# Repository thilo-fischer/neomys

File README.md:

# neomys
Driver software for my Teensy-based DIY keyboard for the Neo2 keyboard layout

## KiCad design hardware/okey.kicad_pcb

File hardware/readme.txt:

Directory includes the schematics and PCB design used to build hardware of Okey adaptations.

The EDA software used is KiCad, http://kicad-pcb.org/. As Okey, KiCad is open source such that anybody can use the software free of charge. (There are some free versions of commercial EDA software available, but those have special restrictions which makes them inapplicable for most Okey PCBs, e.g. PCB sizes below 80 x 100 mm.)

Most schematics and PCB files use parts not (yet) available from the standard libraries that come with KiCad. These parts are taken from 3rd party library files that can be found in the internet. Due to unclear license and copyright constraints of those 3rd party library, these library files are not included in the Okey repository. Currently, these parts listed below are taken from the referenced libraries:

Cherry MX switches
  http://www.key64.org/downloads/key64-20120707.tgz => cherry.lib

7-stage binary counter 4024
  http://www.kicadlib.org/modules/gajda_cmosieee.lib.zip

8 bit SIPO shift latch register 4094N
  https://github.com/musa/kicad-library/blob/master/library/40xx.lib

Todo-List

- Constoller board: Change BCE Transistors to more common CBE Transistors
- Extra buttons board: Adapt button footprint to match 2.54 mm raster *and* 4.50/6.50 mm (6 mm) buttons (e.g. JTP-1130)

Notes

#Grid used to place Cherry MX switches and route tracks: 18.5mm x 18.5mm, 1.85mm x 1.85mm

Grid used to place Cherry MX switches: 18.415mm x 18.415mm, 2.301875mm x 0.3175mm
  2.54 * 7.25 = 18.415
  18.415 / 8 = 2.301875
  2.54 / 8 = 0.3175

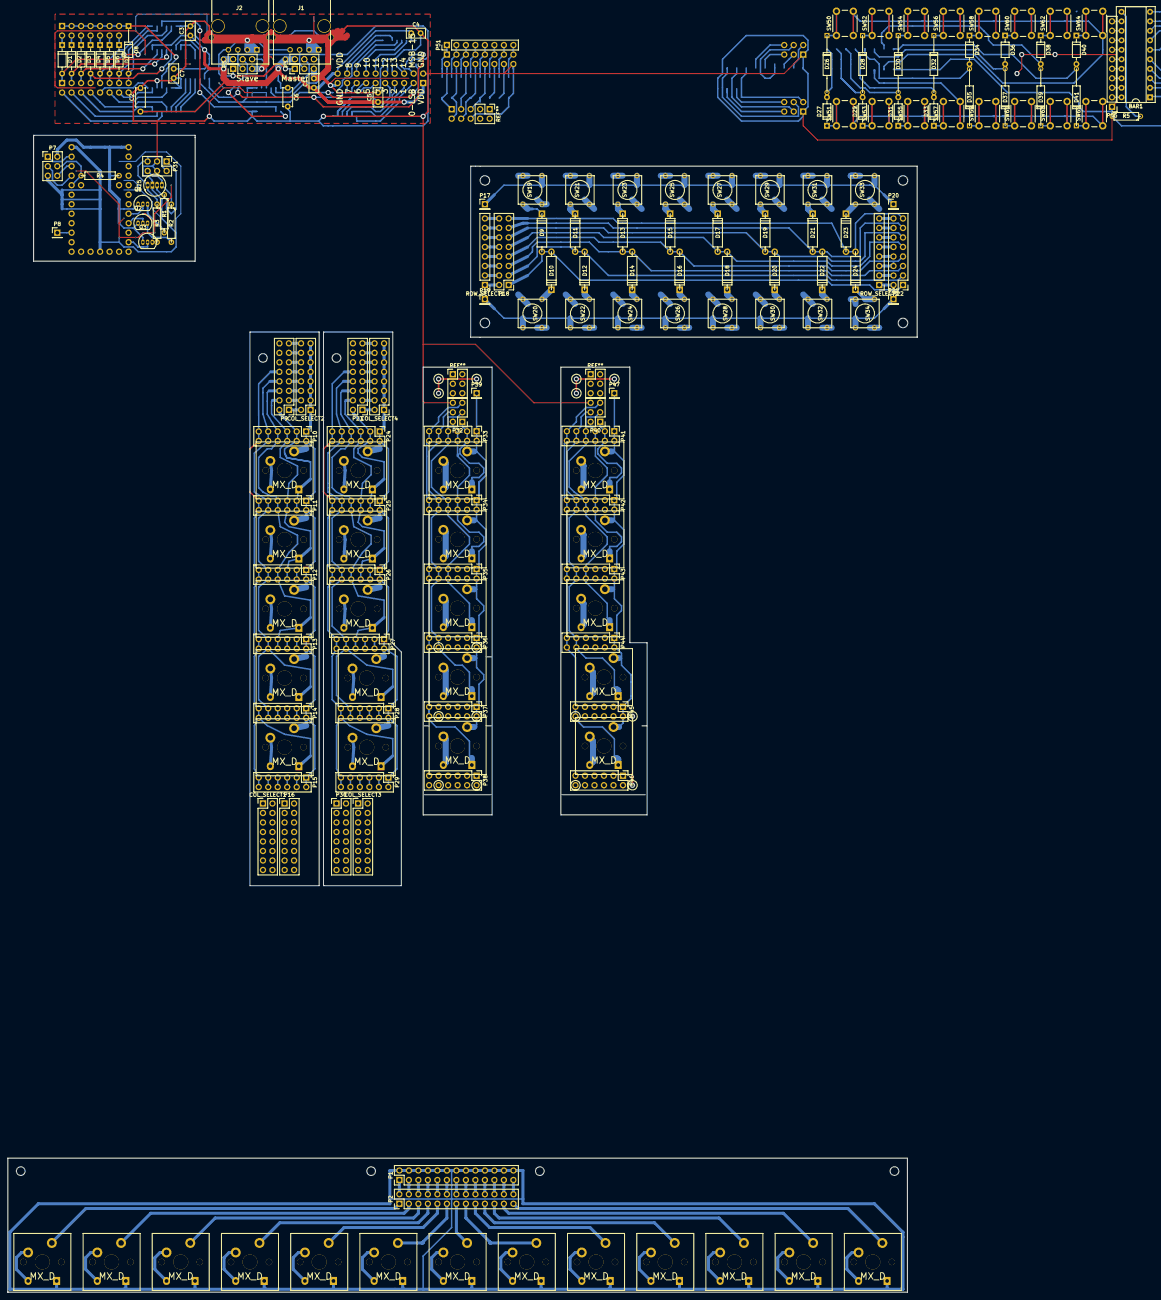
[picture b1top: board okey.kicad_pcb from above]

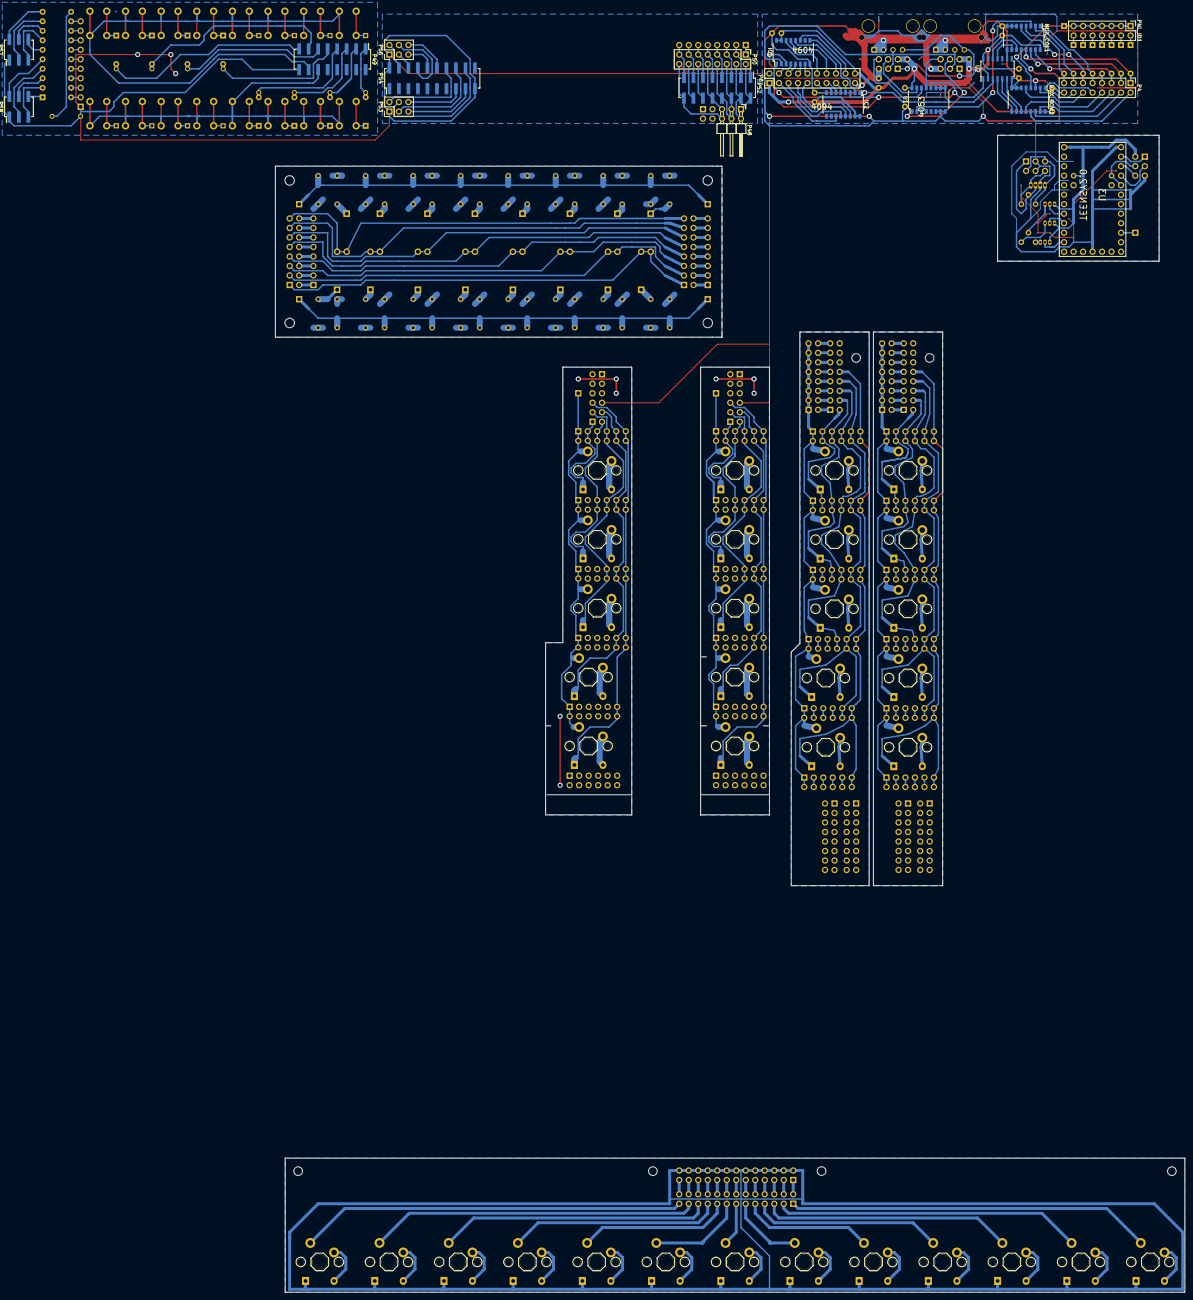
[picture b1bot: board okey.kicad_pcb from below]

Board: 2 copper layers, 196 parts (18 on the bottom side), 300 nets.

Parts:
BAR1: DOT-BAR2; DIP-20_W7.62mm_Socket
C1: 1uF; C_Disc_D5.0mm_W2.5mm_P2.50mm
C2, C6: 100nF; C_Disc_D5.0mm_W2.5mm_P5.00mm
C3, C4, C5, C7: 100nF; C_Disc_D5.0mm_W2.5mm_P2.50mm
COL_SELECT1, COL_SELECT2, COL_SELECT3, COL_SELECT4: CONN_02X08; Pin_Header_Straight_2x08_Pitch2.54mm
D1, D2, D3, D4, D5, D6, D7, D27, D29, D31, D33, D34, D36, D38, D40: D; D_DO-35_SOD27_P7.62mm_Horizontal
D8: D; D_DO-35_SOD27_P12.70mm_Horizontal
D9, D10, D11, D12, D13, D14, D15, D16, D17, D18, D19, D20, D21, D22, D23, D24: D; D4
D25: LED_RCBG; LED-RGB-5MM_Common_Cathode
D26, D28, D30, D32, D35, D37, D39, D41: D; D6_small
IC1, IC2: 4094N; SOP-16_4.4x10.4mm_Pitch1.27mm
J1, J2: RJ45; RJ45_8G
MUX_COL1: 4051; SOP-16_4.4x10.4mm_Pitch1.27mm
MUX_ROW1: 4051; SOP-16_4.4x10.4mm_Pitch1.27mm
P1: ROW_JMP; Pin_Header_Straight_2x13_Pitch2.54mm
P2: CONN_02X13; Pin_Header_Straight_2x13_Pitch2.54mm
P3, P5, P7, P31, P32, P40: CONN_02X03; Pin_Header_Straight_2x03_Pitch2.54mm
P4, P9, P16, P18, P22, P23, P30, P50: CONN_02X08; Pin_Header_Straight_2x08_Pitch2.54mm
P6: CONN_02X10; Pin_Header_Straight_2x10_Pitch2.54mm
P8, P17, P19, P20, P21, P39, P47: CONN_01X01; Pin_Header_Straight_1x01_Pitch2.54mm
P10, P11, P12, P13, P14, P15, P24, P25, P26, P27, P28, P29, P33, P34, P35, P36, P37, P38, P41, P42, P43, P44, P45, P46: CONN_02X06; Pin_Header_Straight_2x06_Pitch2.54mm
P48: CONN_02X03; Pin_Header_Angled_2x03_Pitch2.54mm
P49, P52: CONN_02X08; Pin_Header_Straight_2x08_Pitch2.54mm_SMD
P51: CONN_01X08; Pin_Header_Straight_1x08_Pitch2.54mm
P53, P56: CONN_01X06; Pin_Header_Straight_2x03_Pitch2.54mm
P54: CONN_02X10; Pin_Header_Straight_2x10_Pitch2.54mm_SMD
P55: R_SIP_x9_390; Pin_Header_Straight_1x10_Pitch2.54mm
P57, P58: CONN_01X06; Pin_Header_Straight_2x03_Pitch2.54mm_SMD
PNL_ID1: CONN_02X07; Pin_Header_Straight_2x07_Pitch2.54mm
Q1, Q2, Q3: Q_NPN_CBE; TO-92_Inline_Narrow_Oval
R1, R2, R3, R4: R; R4
R5: R270; R3
ROW_SELECT1, ROW_SELECT2: CONN_01X08; Pin_Header_Straight_1x08_Pitch2.54mm
SW1, SW2, SW3, SW4, SW5, SW6, SW7, SW8, SW9, SW10, SW11, SW12, SW13, SW14, SW15, SW16, SW17, SW18, SW35, SW36, SW37, SW38, SW39, SW40, SW41, SW42, SW43, SW44, SW45, SW46, SW47, SW48, SW49: MX_D; SW_PCB_4PIN
SW19, SW20, SW21, SW22, SW23, SW24, SW25, SW26, SW27, SW28, SW29, SW30, SW31, SW32, SW33, SW34: SW_PUSH; SW_PUSH_SMALL
SW50, SW51, SW52, SW53, SW54, SW55, SW56, SW57, SW58, SW59, SW60, SW61, SW62, SW63, SW64, SW65: SW_PUSH; SW_PUSH_6mm
U1: 4053; SOP-16_4.4x10.4mm_Pitch1.27mm
U2: 4024; SOIC-14_3.9x8.7mm_Pitch1.27mm
U3: TEENSY2.0; TEENSY_2.0

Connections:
/Cherry-MX Switches Row 3x up to 8x /ROW: P1.2, P1.4, P1.6, P1.8, P1.10, P1.12, P1.14, P1.16, P1.18, P1.20, P1.22, P1.24, P1.26, SW1.4, SW2.4, SW3.4, SW4.4, SW5.4, SW6.4, SW7.4, SW8.4, SW9.4, SW10.4, SW11.4, SW12.4, SW13.4
/Panel Generic SPI01/PNL_BUS_OUT: J2.4, P5.4, U1.1
/Panel Generic SPI01/clock: J1.2, P3.6, U1.14
/Panel Generic SPI01/miso: J1.4, P3.4, U1.15
/Panel Generic SPI01/reset: J1.7, J2.7, P3.1, P5.1, U2.2
GND: C1.2, C2.2, C3.2, C4.2, C5.2, C6.2, C7.2, D25.2, IC1.8, IC2.8, J1.1, J1.3, J1.9, J2.1, J2.3, J2.9, MUX_COL1.6, MUX_COL1.7, MUX_COL1.8, MUX_ROW1.3, MUX_ROW1.6, MUX_ROW1.7, MUX_ROW1.8, P3.5, P4.16, P5.5, P6.2, P6.19, P7.5, P31.3, P31.4, P32.6, P40.6, P48.6, P49.16, P50.16, P52.16, P53.1, P54.2, P54.19, P55.1, P56.1, P57.1, P58.1, R5.2, U1.6, U1.7, U1.8, U2.7, U3.15, U3.29
unnamed: BAR1.1, P58.6
unnamed: BAR1.2, P58.5
unnamed: BAR1.3, P58.4
unnamed: BAR1.4, P58.3
unnamed: BAR1.5, P58.2
unnamed: BAR1.6, P57.6
unnamed: BAR1.7, P57.5
unnamed: BAR1.8, P57.4
unnamed: BAR1.9, P57.3
unnamed: BAR1.10, P57.2
unnamed: BAR1.11, R5.1
unnamed: BAR1.12, P55.10
unnamed: BAR1.13, P55.9
unnamed: BAR1.14, P55.8
unnamed: BAR1.15, P55.7
unnamed: BAR1.16, P55.6
unnamed: BAR1.17, P55.5
unnamed: BAR1.18, P55.4
unnamed: BAR1.19, P55.3
unnamed: BAR1.20, P55.2
unnamed: COL_SELECT1.1, COL_SELECT1.3, COL_SELECT1.5, COL_SELECT1.7, COL_SELECT1.9, COL_SELECT1.11, COL_SELECT1.13, COL_SELECT1.15, COL_SELECT2.1, COL_SELECT2.3, COL_SELECT2.5, COL_SELECT2.7, COL_SELECT2.9, COL_SELECT2.11, COL_SELECT2.13, COL_SELECT2.15, P10.1, P10.2, P11.1, P11.2, P12.1, P12.2, P13.1, P13.2, P14.1, P14.2, P15.1, P15.2, SW14.1, SW15.1, SW16.1, SW17.1, SW18.1
unnamed: COL_SELECT1.2, P16.1
unnamed: COL_SELECT1.4, P16.3
unnamed: COL_SELECT1.6, P16.5
unnamed: COL_SELECT1.8, P16.7
unnamed: COL_SELECT1.10, P16.9
unnamed: COL_SELECT1.12, P16.11
unnamed: COL_SELECT1.14, P16.13
unnamed: COL_SELECT1.16, P16.15
unnamed: COL_SELECT2.2, P9.1
unnamed: COL_SELECT2.4, P9.3
unnamed: COL_SELECT2.6, P9.5
unnamed: COL_SELECT2.8, P9.7
unnamed: COL_SELECT2.10, P9.9
unnamed: COL_SELECT2.12, P9.11
unnamed: COL_SELECT2.14, P9.13
unnamed: COL_SELECT2.16, P9.15
unnamed: COL_SELECT3.1, COL_SELECT3.3, COL_SELECT3.5, COL_SELECT3.7, COL_SELECT3.9, COL_SELECT3.11, COL_SELECT3.13, COL_SELECT3.15, COL_SELECT4.1, COL_SELECT4.3, COL_SELECT4.5, COL_SELECT4.7, COL_SELECT4.9, COL_SELECT4.11, COL_SELECT4.13, COL_SELECT4.15, P24.1, P24.2, P25.1, P25.2, P26.1, P26.2, P27.1, P27.2, P28.1, P28.2, P29.1, P29.2, SW35.1, SW36.1, SW37.1, SW38.1, SW39.1
unnamed: COL_SELECT3.2, P30.1
unnamed: COL_SELECT3.4, P30.3
unnamed: COL_SELECT3.6, P30.5
unnamed: COL_SELECT3.8, P30.7
unnamed: COL_SELECT3.10, P30.9
unnamed: COL_SELECT3.12, P30.11
unnamed: COL_SELECT3.14, P30.13
unnamed: COL_SELECT3.16, P30.15
unnamed: COL_SELECT4.2, P23.1
unnamed: COL_SELECT4.4, P23.3
unnamed: COL_SELECT4.6, P23.5
unnamed: COL_SELECT4.8, P23.7
unnamed: COL_SELECT4.10, P23.9
unnamed: COL_SELECT4.12, P23.11
unnamed: COL_SELECT4.14, P23.13
unnamed: COL_SELECT4.16, P23.15
unnamed: D1.1, PNL_ID1.2
unnamed: D1.2, MUX_COL1.13, P4.1
unnamed: D2.1, PNL_ID1.4
unnamed: D2.2, MUX_COL1.14, P4.3
unnamed: D3.1, PNL_ID1.6
unnamed: D3.2, MUX_COL1.15, P4.5
unnamed: D4.1, PNL_ID1.8
unnamed: D4.2, MUX_COL1.12, P4.7
unnamed: D5.1, PNL_ID1.10
unnamed: D5.2, MUX_COL1.1, P4.9
unnamed: D6.1, PNL_ID1.12
unnamed: D6.2, MUX_COL1.5, P4.11
unnamed: D7.1, PNL_ID1.14
unnamed: D7.2, MUX_COL1.2, P4.13
unnamed: D8.1, MUX_ROW1.4, PNL_ID1.1, PNL_ID1.3, PNL_ID1.5, PNL_ID1.7, PNL_ID1.9, PNL_ID1.11, PNL_ID1.13
unnamed: D8.2, MUX_COL1.4, P4.15
unnamed: D9.1, SW19.1
unnamed: D10.1, SW20.1
unnamed: D9.2, D10.2, P18.1, P22.1
unnamed: D11.1, SW21.1
unnamed: D11.2, D12.2, P18.3, P22.3
unnamed: D12.1, SW22.1
unnamed: D13.1, SW23.1
unnamed: D13.2, D14.2, P18.5, P22.5
unnamed: D14.1, SW24.1
unnamed: D15.1, SW25.1
unnamed: D15.2, D16.2, P18.7, P22.7
unnamed: D16.1, SW26.1
unnamed: D17.1, SW27.1
unnamed: D17.2, D18.2, P18.9, P22.9
unnamed: D18.1, SW28.1
unnamed: D19.1, SW29.1
unnamed: D19.2, D20.2, P18.11, P22.11
unnamed: D20.1, SW30.1
unnamed: D21.1, SW31.1
unnamed: D21.2, D22.2, P18.13, P22.13
unnamed: D22.1, SW32.1
unnamed: D23.1, SW33.1
unnamed: D23.2, D24.2, P18.15, P22.15
unnamed: D24.1, SW34.1
unnamed: D25.1, P31.2, P31.5, R3.1
unnamed: D25.3, P31.1, R1.1
unnamed: D25.4, P31.6, R2.1
unnamed: D26.1, SW50.1
unnamed: D26.2, D27.2, P49.1
unnamed: D27.1, SW51.1
unnamed: D28.1, SW52.1
unnamed: D28.2, D29.2, P49.3
unnamed: D29.1, SW53.1
unnamed: D30.1, SW54.1
unnamed: D30.2, D31.2, P49.5
unnamed: D31.1, SW55.1
unnamed: D32.1, SW56.1
unnamed: D32.2, D33.2, P49.7
unnamed: D33.1, SW57.1
unnamed: D34.1, SW58.1
unnamed: D34.2, D35.2, P49.9
unnamed: D35.1, SW59.1
unnamed: D36.1, SW60.1
unnamed: D36.2, D37.2, P49.11
unnamed: D37.1, SW61.1
unnamed: D38.1, SW62.1
unnamed: D38.2, D39.2, P49.13
unnamed: D39.1, SW63.1
unnamed: D40.1, SW64.1
unnamed: D40.2, D41.2, P49.15
unnamed: D41.1, SW65.1
unnamed: IC1.1, IC2.1, U1.9, U1.10, U1.11, U2.3
unnamed: IC1.2, J1.5, J2.5, P3.3, P5.3
unnamed: IC1.3, IC2.3, U1.12, U2.1
unnamed: IC1.4, P6.4
unnamed: IC1.5, P6.6
unnamed: IC1.6, P6.8
unnamed: IC1.7, P6.10
unnamed: IC1.9, IC2.2
unnamed: IC1.11, P6.18
unnamed: IC1.12, P6.16
unnamed: IC1.13, P6.14
unnamed: IC1.14, P6.12
unnamed: IC2.4, P6.17
unnamed: IC2.5, P6.15
unnamed: IC2.6, P6.13
unnamed: IC2.7, P6.11
unnamed: IC2.11, P6.3
unnamed: IC2.12, P6.5
unnamed: IC2.13, P6.7
unnamed: IC2.14, P6.9
unnamed: J2.2, P5.6, U1.13
unnamed: MUX_COL1.3, U1.2
unnamed: MUX_COL1.9, U2.9
unnamed: MUX_COL1.10, U2.11
unnamed: MUX_COL1.11, U2.12
unnamed: MUX_ROW1.1, P4.10
unnamed: MUX_ROW1.2, P4.14
unnamed: MUX_ROW1.5, P4.12
unnamed: MUX_ROW1.9, U2.4
unnamed: MUX_ROW1.10, U2.5
unnamed: MUX_ROW1.11, U2.6
unnamed: MUX_ROW1.12, P4.8
unnamed: MUX_ROW1.13, P4.2
unnamed: MUX_ROW1.14, P4.4
unnamed: MUX_ROW1.15, P4.6
unnamed: P1.1, P2.2
unnamed: P1.3, P2.4
unnamed: P1.5, P2.6
unnamed: P1.7, P2.8
unnamed: P1.9, P2.10
unnamed: P1.11, P2.12
unnamed: P1.13, P2.14
unnamed: P1.15, P2.16
unnamed: P1.17, P2.18
unnamed: P1.19, P2.20
unnamed: P1.21, P2.22
unnamed: P1.23, P2.24
unnamed: P1.25, P2.26
unnamed: P2.1, SW4.1
unnamed: P2.3, SW5.1
unnamed: P2.5, SW6.1
unnamed: P2.7, SW7.1
unnamed: P2.9, SW8.1
unnamed: P2.11, SW1.1
unnamed: P2.13, SW2.1
unnamed: P2.15, SW3.1
unnamed: P2.17, SW9.1
unnamed: P2.19, SW10.1
unnamed: P2.21, SW11.1
unnamed: P2.23, SW12.1
unnamed: P2.25, SW13.1
unnamed: P7.1, U3.28
unnamed: P7.3, U3.26
unnamed: P7.4, R4.2, U3.25
unnamed: P7.6, U3.27
unnamed: P8.1, U3.20
unnamed: P9.2, P10.3, P10.4, P11.3, P11.4, P12.3, P12.4, P13.3, P13.4, P14.3, P14.4, P15.3, P15.4, P16.2, SW14.4
unnamed: P9.4, P10.5, P10.6, P11.5, P11.6, P12.5, P12.6, P13.5, P13.6, P14.5, P14.6, P15.5, P15.6, P16.4, SW15.4
unnamed: P9.6, P10.7, P10.8, P11.7, P11.8, P12.7, P12.8, P13.7, P13.8, P14.7, P14.8, P15.7, P15.8, P16.6, SW16.4
unnamed: P9.8, P10.9, P10.10, P11.9, P11.10, P12.9, P12.10, P13.9, P13.10, P14.9, P14.10, P15.9, P15.10, P16.8, SW17.4
unnamed: P9.10, P10.11, P10.12, P11.11, P11.12, P12.11, P12.12, P13.11, P13.12, P14.11, P14.12, P15.11, P15.12, P16.10, SW18.4
unnamed: P17.1, P20.1, SW19.2, SW21.2, SW23.2, SW25.2, SW27.2, SW29.2, SW31.2, SW33.2
unnamed: P18.2, ROW_SELECT1.1
unnamed: P18.4, ROW_SELECT1.2
unnamed: P18.6, ROW_SELECT1.3
unnamed: P18.8, ROW_SELECT1.4
unnamed: P18.10, ROW_SELECT1.5
unnamed: P18.12, ROW_SELECT1.6
unnamed: P18.14, ROW_SELECT1.7
unnamed: P18.16, ROW_SELECT1.8
unnamed: P19.1, P21.1, SW20.2, SW22.2, SW24.2, SW26.2, SW28.2, SW30.2, SW32.2, SW34.2
unnamed: P22.2, ROW_SELECT2.1
unnamed: P22.4, ROW_SELECT2.2
unnamed: P22.6, ROW_SELECT2.3
unnamed: P22.8, ROW_SELECT2.4
unnamed: P22.10, ROW_SELECT2.5
unnamed: P22.12, ROW_SELECT2.6
unnamed: P22.14, ROW_SELECT2.7
unnamed: P22.16, ROW_SELECT2.8
unnamed: P23.2, P24.3, P24.4, P25.3, P25.4, P26.3, P26.4, P27.3, P27.4, P28.3, P28.4, P29.3, P29.4, P30.2, SW35.4
unnamed: P23.4, P24.5, P24.6, P25.5, P25.6, P26.5, P26.6, P27.5, P27.6, P28.5, P28.6, P29.5, P29.6, P30.4, SW36.4
unnamed: P23.6, P24.7, P24.8, P25.7, P25.8, P26.7, P26.8, P27.7, P27.8, P28.7, P28.8, P29.7, P29.8, P30.6, SW37.4
unnamed: P23.8, P24.9, P24.10, P25.9, P25.10, P26.9, P26.10, P27.9, P27.10, P28.9, P28.10, P29.9, P29.10, P30.8, SW38.4
unnamed: P23.10, P24.11, P24.12, P25.11, P25.12, P26.11, P26.12, P27.11, P27.12, P28.11, P28.12, P29.11, P29.12, P30.10, SW39.4
unnamed: P32.1, P33.3, P33.4, SW40.4
unnamed: P32.2, P33.5, P33.6, P34.5, P34.6, SW41.4
unnamed: P32.3, P33.7, P33.8, P34.7, P34.8, P35.7, P35.8, SW42.4
unnamed: P32.4, P33.9, P33.10, P34.9, P34.10, P35.9, P35.10, P36.9, P36.10, SW43.4
unnamed: P32.5, P33.11, P33.12, P34.11, P34.12, P35.11, P35.12, P36.11, P36.12, P37.11, P37.12, SW44.4
unnamed: P33.1, P33.2, P34.1, P34.2, P35.1, P35.2, P36.1, P36.2, P37.1, P37.2, P39.1, SW40.1, SW41.1, SW42.1, SW43.1, SW44.1
unnamed: P40.1, P41.3, P41.4, SW45.4
unnamed: P40.2, P41.5, P41.6, P42.5, P42.6, SW46.4
unnamed: P40.3, P41.7, P41.8, P42.7, P42.8, P43.7, P43.8, SW47.4
unnamed: P40.4, P41.9, P41.10, P42.9, P42.10, P43.9, P43.10, P44.9, P44.10, SW48.4
unnamed: P40.5, P41.11, P41.12, P42.11, P42.12, P43.11, P43.12, P44.11, P44.12, P45.11, P45.12, SW49.4
unnamed: P41.1, P41.2, P42.1, P42.2, P43.1, P43.2, P44.1, P44.2, P45.1, P45.2, P47.1, SW45.1, SW46.1, SW47.1, SW48.1, SW49.1
unnamed: P48.1, P50.2, P52.2
unnamed: P48.2, P50.4, P52.4
unnamed: P48.3, P50.6, P52.6
unnamed: P48.4, P50.8, P52.8
unnamed: P48.5, P50.10, P52.10
unnamed: P49.12, SW51.2, SW53.2, SW55.2, SW57.2, SW59.2, SW61.2, SW63.2, SW65.2
unnamed: P49.14, SW50.2, SW52.2, SW54.2, SW56.2, SW58.2, SW60.2, SW62.2, SW64.2
unnamed: P50.1, P51.1, P52.1
unnamed: P50.3, P51.2, P52.3
unnamed: P50.5, P51.3, P52.5
unnamed: P50.7, P51.4, P52.7
unnamed: P50.9, P51.5, P52.9
unnamed: P50.11, P51.6, P52.11
unnamed: P50.12, P52.12
unnamed: P50.13, P51.7, P52.13
unnamed: P50.14, P52.14
unnamed: P50.15, P51.8, P52.15
unnamed: P53.2, P54.14
unnamed: P53.3, P54.16
unnamed: P53.4, P54.18
unnamed: P53.5, P54.17
unnamed: P53.6, P54.15
unnamed: P54.4, P56.2
unnamed: P54.6, P56.3
unnamed: P54.8, P56.4
unnamed: P54.10, P56.5
unnamed: P54.12, P56.6
unnamed: Q1.2, U3.8
unnamed: Q1.3, R1.2
unnamed: Q2.2, U3.9
unnamed: Q2.3, R2.2
unnamed: Q3.2, U3.11
unnamed: Q3.3, R3.2
unnamed: SW1.2, SW1.3
unnamed: SW2.2, SW2.3
unnamed: SW3.2, SW3.3
unnamed: SW4.2, SW4.3
unnamed: SW5.2, SW5.3
unnamed: SW6.2, SW6.3
unnamed: SW7.2, SW7.3
unnamed: SW8.2, SW8.3
unnamed: SW9.2, SW9.3
unnamed: SW10.2, SW10.3
unnamed: SW11.2, SW11.3
unnamed: SW12.2, SW12.3
unnamed: SW13.2, SW13.3
unnamed: SW14.2, SW14.3
unnamed: SW15.2, SW15.3
unnamed: SW16.2, SW16.3
unnamed: SW17.2, SW17.3
unnamed: SW18.2, SW18.3
unnamed: SW35.2, SW35.3
unnamed: SW36.2, SW36.3
unnamed: SW37.2, SW37.3
unnamed: SW38.2, SW38.3
unnamed: SW39.2, SW39.3
unnamed: SW40.2, SW40.3
unnamed: SW41.2, SW41.3
unnamed: SW42.2, SW42.3
unnamed: SW43.2, SW43.3
unnamed: SW44.2, SW44.3
unnamed: SW45.2, SW45.3
unnamed: SW46.2, SW46.3
unnamed: SW47.2, SW47.3
unnamed: SW48.2, SW48.3
unnamed: SW49.2, SW49.3
VDD: C1.1, C2.1, C3.1, C4.1, C5.1, C6.1, C7.1, IC1.15, IC1.16, IC2.15, IC2.16, J1.6, J1.8, J2.6, J2.8, MUX_COL1.16, MUX_ROW1.16, P3.2, P5.2, P6.1, P6.20, P7.2, P54.1, P54.20, Q1.1, Q2.1, Q3.1, R4.1, U1.16, U2.14, U3.1

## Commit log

2015-02-04 fixed some compile issues
2015-02-04 fix compile errors
2015-02-04 drop F-key row
2015-02-04 key mapping for DE
2015-02-06 split to several files
2015-02-06 started to implement key press evluation
2015-02-06 refactor keymappings.h
2015-02-07 started implementation of approch to communicate key_ids of all pressed keys from slave to master
2015-02-07 started implementation of approch to communicate key_ids of only changed keys from slave to master
2015-02-08 restructure keymap array definition
2015-02-10 fix keymap table (DE ROW_NUM level2)
2015-02-10 restructure and refactor keymappings
2015-02-11 finished writing down all neomys code that's currently on my mind -- let's see what this code does when put onto a teensy ...
2015-02-11 fix compile errors, small cleanup
2015-02-12 lot's of dirty test code ...
2015-02-13 started drawing layout svg
2015-02-13 layout: center key cap lable paragraph alignment
2015-02-13 slave controller successfully transmitting key states via UART
2015-02-15 put keymap to progmem some dirty code for test and debug aid
2015-02-15 master controller tested successfully
2015-02-15 communication master/slave working (but with minor issues)
2015-02-15 master/slave communication working properly
2015-02-16 Makefile builds binaries for master and slave controller
2015-02-16 layout.svg: ...
2015-02-17 layout: copper
2015-02-17 layout: copper.
2015-02-17 layout: right level3 modifier ...
2015-02-17 layout: right level3 modifier.
2015-02-18 layout: reworking PCB copper ...
2015-02-18 layout: reworked PCB.
2015-02-18 layout.svg ...
2015-02-18 layout.svg: copyright and license note
2015-03-11 fixed compilation error
2015-03-12 fix warning LED
2015-03-13 fix key mappings in space row
2015-03-13 fix communication error recovery
2015-03-13 output some more information for debugging
2015-03-14 separate teensy code library code from neomys code
2015-03-14 Makefile: flash_% target
2015-03-14 separate independent code sections and split to several files
2015-03-14 Makefile: wait for device when flashing
2015-03-14 fix master-slave-confusion
2015-03-14 rework keymap ...
2015-03-15 ... rework keymap ...
2015-03-15 ... rework keymap (compiling again :) ) ...
2015-03-16 ... rework keymap (add debugging output) ...
2015-03-16 ... still bugfixing ...
2015-03-16 ... fix: index array by level ...
2015-03-16 ... fix: key press/release/target_layout confusion ...
2015-03-16 ... rework keymap.
2015-03-17 layout.svg: add some more keys and define most of LEVEL4_MOUSE
2015-03-17 add more keys (esp. on LEVEL4_MOUSE), some cleanup, minor bugfixing
2015-03-17 fix bug: right shift key locking to level2
2015-03-17 cleaup and minor bugfixing
2015-03-18 fix neo exclamation mark
2015-03-18 fix neo tab
2015-03-18 dealing with level locking (esp wrt Neo) ...
2015-03-18 ... dealing with level locking (esp wrt Neo) ...
2015-03-18 Revert "cleaup and minor bugfixing"
    This reverts commit 493fc84233313aec24e5559f4f4a24b2a205ab41.
    Conflicts:
    keytranslation.c
2015-03-18 cherry-picked from "cleaup and minor bugfixing", reverted removing of kf_level2/3 functions
    Conflicts:
    keytranslation.c
2015-03-18 ... dealing with level locking (esp wrt Neo) -- hide level locking from Neo ...
2015-03-18 TL_APPLE_DE ...
2015-03-18 fix bug with target layout selection key
2015-03-18 ... TL_APPLE_DE.
2015-03-19 ... dealing with level locking (esp wrt Neo) => Any level locking will be hidden from Neo hosts.
2015-03-19 minor cleanup
2015-03-19 changed position of ALT keys, addad some functions to the keys operated by the thumbs
2015-03-19 add F1--F12 keys
2015-03-19 add some more punctuation characters for TL_NEO
2015-03-19 space@L4 = Return, minor cleanup
2015-03-20 cleanup
2015-03-20 layout.svg metadata
2015-03-20 explaining the neomys design ...
2015-03-20 ... explaining the neomys design
2015-03-20 move key_6 to the 'right' side
    This deviates from regular keyboards with divided key fields, but feels much better when typing :)
2015-03-20 ... intermediate ABOUT.txt ...
2015-04-19 layout.svg: fix typo
2015-04-19 comment helping in interpretation of uart dbg output
2015-04-19 change order of key/modifier key release processing
2015-04-19 quickfix to handle modifier key release w/o modified key release
2015-04-19 switching target layout and locking modes of target layout
2015-04-19 fix numblock for Neo2 target layout
2015-04-19 source code documentation
2015-04-21 increase UART baudrate
2015-04-26 increase UART baudrate touch up, increase main loop frequency
2015-04-26 fix apple caret & tilde
2015-04-26 quickfix slave not sending keypress information
2015-04-26 revert older, incorrect quickfix that tried to handle modifier key release w/o modified key release
2015-04-26 check out bugfix for shift key not getting released
2015-04-26 comment in source code how to fix problems with cevrons and backtick with apple OsX
2015-04-26 file structure ...
2015-11-15 introducing variant handling for IO ...
2015-12-12 first draft for flexible and modular implementation using `panels'
2015-12-13 prototypic implementation of restructured code written down (not compiling yet)
2015-12-14 implement methods to address specific elements in the ksw_states buffers
2015-12-14 move module-unspecific helper functions to a utils module
2015-12-19 fixing compile errors ...
2015-12-19 ... fixing compile errors ...
2015-12-19 ... fixing compile errors (rename some adaptation files) ...
2015-12-19 ... fixing compile errors (compiles, but does not link yet) ...
2015-12-20 cleanup deprecated files
2015-12-20 ... fixing build errors.
2015-12-20 add support for Teensy++ 2.0 controller
2015-12-20 fix Makefile flash, comments
2015-12-20 quick and dirty code manipulations for debugging of the current implementation
2015-12-20 fix cpu frequency
2015-12-31 bugfix: read invalid elements in panel_processing array
2015-12-31 bugfix: drive reset pin
2015-12-31 bugfix: output data
2015-12-31 Change meaning of bits in keystate arrays: 1 means key pressed, 0 means not pressed. Bugfix: Initialization value of keystate arrays.
2015-12-31 remove code from debuging and testing
2015-12-31 add code for debuging and testing
2015-12-31 minor code cleanup
2015-12-31 fix: call usb keyboard init function => key switch activation results in characters appearing on the host's screen :)
2016-01-03 fix last panel SIPO register strobe
2016-01-04 initial PCB KiCad project
2016-01-05 PCB layout ...
2016-01-05 ... PCB layout ...
2016-01-05 ... PCB layout: all lines connected ...
2016-01-05 ... PCB layout: reducing pcb width ...
2016-01-05 ... PCB: shrink SPI board, add filled zones, connect key switch row ...
2016-01-06 ... main PCB
2016-01-06 hardware schematics and PCB in repository
2016-01-06 bugfix: drive reset pin
    y# .dep/
2016-01-06 code for uart dbg messages
2016-01-06 bugfix: call NULL as function pointer
2016-01-06 fix wrong connetion between counter bits and row/col multiplexer
2016-01-06 PCB: optimized routing
2016-01-06 PCB: optimize routing
2016-01-12 misc PCB design
2016-01-13 ... PCB design
2016-01-13 PCB fix: add pullup resistor
2016-01-13 rm okey.net (generated file)
2016-01-13 PCB fix: dimensions on extra button board
2016-01-13 PCB todo notes
2016-02-12 reduce controller's clock frequency to reduce SPI rate to a less error prone speed level
2016-02-12 fix swapped neomys panels
2016-02-12 fix build error from merge
2016-03-01 PCD design: increase distance of too close wires
2016-03-05 debug messaging ...
2016-03-11 ... debug messaging ...
2016-03-11 minor Makefile enhancements and cleanup
2016-03-11 notifications ...
2016-03-12 git repo cleanup
2016-03-12 fix Makefile
2016-03-16 ... dbg msging ...
2016-03-16 ... add dbg and indication ...
2016-03-16 ... fix some compile errors ...
2016-03-16 ... fix compile errors ...
2016-03-18 ... fix compile errors and bugfix ...
2016-03-20 add debug message output
2016-03-20 ... fix compile warning
2016-03-20 dbg: uart prefix/suffix
2016-03-20 debug output
2016-03-20 'neutralize' deprecated code
2016-03-20 bugfix: stucking levels
2016-03-25 support target layout indication LEDs, extra buttons support target layout switching
2016-03-25 shorthand string debug command for printf debugging
2016-04-23 bugfix panel output data
2016-04-23 activate keys in extra rows and cleanup, extend key code width 8->16 bit
2016-04-26 quickfix for key jamming bug
2016-04-26 add some debug output
2016-06-11 stencil for housing
2016-10-20 bugfix for occasional modifier jam
2016-10-20 stencil for housing: add cutting aid markings
2016-11-29 further housing development
2016-12-03 extra keys layout: switch caps lock and num lock
2016-12-03 housing: key column bars
2017-03-11 housing
2017-04-01 hardware: notes
2017-05-17 hardware: reworked key columns PCB
2017-05-26 squash! hardware: reworked key columns PCB
2017-05-27 tidy up KSW_BUS connector
2017-05-27 hardware: add bypass capacitors
2017-05-28 hardware: rework SPI board as SMD board with smaller dimensions ...
2017-05-29 squash! ... hardware: rework SPI board as SMD board with smaller dimensions ...
2017-05-29 squash! ... hardware: rework SPI board as SMD board with smaller dimensions: all lines connected ...
2017-06-01 squash! ... hardware: rework SPI board as SMD board with smaller dimensions: pin header or rj45 connector options ...
2017-06-01 squash! ... hardware: rework SPI board as SMD board with smaller dimensions.
2017-06-02 hardware: misc minor SPI board cleanup
2017-06-02 hardware, SPI-board: RJ45-jack shielding
2017-06-02 hardware, SPI-board: minor cleanup
2017-06-03 hardware, key-columns: cleanup, drill holes, ...
2017-06-03 hardware: rework controller board
2017-06-03 hardware, SPI-board: alibi ground tracks for additional copper filling
2017-06-03 hardware, controller board: reduce space occupied, cleanup, alibi GND tracks for copper areas
2017-06-08 hardware, SPI board: rj45 pin arrangement, rework, cleanup
2017-06-11 hardware: new extra buttons PCB ...
2017-06-20 hardware, SPI-Board: rework
2017-06-21 hardware: KSW_BUS adapter board for reworked SPI board
2017-06-22 hardware: KSW_BUS adapter and extra keys PCB
2017-06-22 hardware: display->bargraph-led schematics
2017-06-24 hardware: display->bargraph-led PCB ...
2017-06-27 ... hardware: display->bargraph-led PCB.
2017-06-27 hardware: cleanup
2017-06-27 hardware: optimize SPI PCB layout ...
2017-10-31 hardware: pcb layout
